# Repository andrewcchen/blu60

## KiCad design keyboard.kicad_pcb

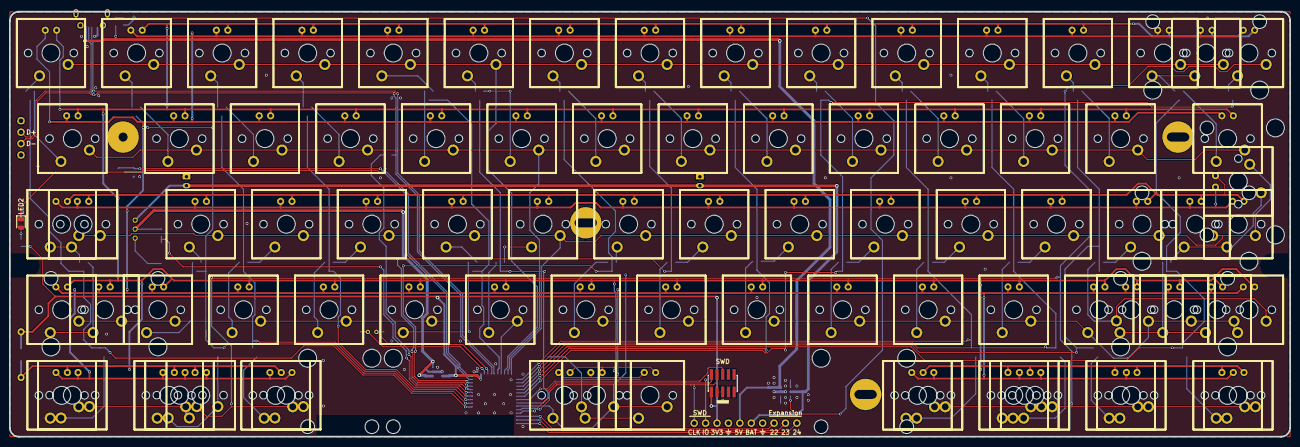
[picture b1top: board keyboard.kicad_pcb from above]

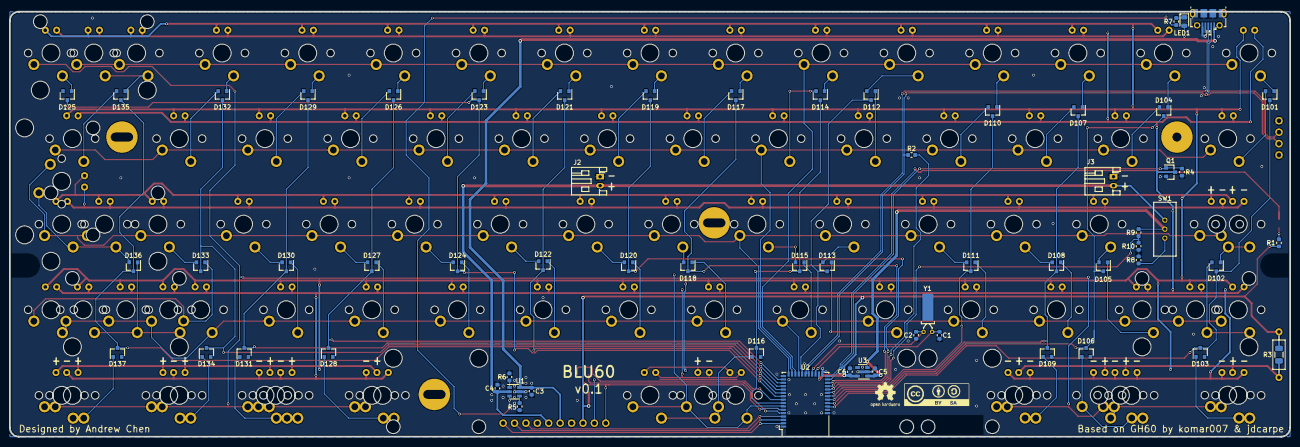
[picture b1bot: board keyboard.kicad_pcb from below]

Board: 2 copper layers, 285.0 x 94.6 mm, 257 parts (64 on the bottom side), 111 nets.

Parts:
C1, C2: C; C_0603_1608Metric
C3, C4, C5, C6: 1uF; C_0603_1608Metric
D101, D102, D104, D105, D107, D108, D110, D111, D112, D113, D114, D115, D117, D118, D119, D120, D121, D122, D123, D124, D126, D127, D129, D130, D132, D133, D135, D136: BAS70-05; SOT-23
D103, D106, D109, D116, D125, D128, D131, D134, D137: BAS70-05; D_SOT-23_ANK
J1: USB_B_Micro; USB_Micro-B_Molex-105017-0001
J2, J3: JST_PH; JST_PH_S2B-PH-K_1x02_P2.00mm_Horizontal
J4: Conn_ARM_JTAG_SWD_10; PinHeader_2x05_P1.27mm_Vertical_SMD
J5: Conn_01x10; PinHeader_1x10_P2.54mm_Vertical
LED1, LED2: Red_LED; LED_0805_2012Metric
LED101, LED102, LED103, LED104, LED105, LED106, LED107, LED108, LED109, LED110, LED111, LED112, LED113, LED114, LED115, LED116, LED117, LED118, LED119, LED120, LED121, LED122, LED123, LED124, LED125, LED126, LED127, LED128, LED129, LED130, LED131, LED132, LED133, LED134, LED135, LED136, LED137, LED138, LED139, LED140, LED141, LED142, LED143, LED144, LED145, LED146, LED147, LED148, LED149, LED150, LED151, LED152, LED153, LED154, LED155, LED156, LED157, LED158, LED159, LED160, LED161, LED162, LED163, LED164, LED165, LED166, LED167, LED168, LED169, LED170, LED171, LED172, LED173, LED174, LED175, LED176, LED177, LED178, LED179, LED180, LED181, LED182, LED183, LED184: LED; MX1A-led_no3d
MK1, MK6: Mounting_Hole; PKRHSL
MK2: Mounting_Hole; PKRHC
MK3, MK4, MK5: Mounting_Hole; PKRH
MXST1, MXST2, MXST3, MXST4, MXST5, MXST6, MXST7, MXST8, MXST9, MXST10, MXST11, MXST12, MXST13, MXST14, MXST15: Cherry_Stabilizer; MXST
Q1: Q_NMOS; SOT-23
R1, R2, R5: 1.5k; R_0603_1608Metric
R3: R; R_Axial_DIN0207_L6.3mm_D2.5mm_P10.16mm_Horizontal
R3#2: R_1206_3216Metric
R4, R9, R10: 100k; R_0603_1608Metric
R6, R7, R8: 10k; R_0603_1608Metric
S101, S102, S103, S105, S107, S109, S110, S111, S113, S116, S117, S118, S119, S120, S122, S123, S124, S125, S126, S127, S128, S129, S130, S131, S132, S133, S134, S137, S138, S139, S140, S141, S142, S143, S144, S145, S146, S147, S148, S149, S150, S151, S152, S154, S155, S156, S157, S158, S160, S161, S162, S163, S164, S167, S168, S173, S174, S176, S177, S180, S184: MX1A
S104, S106, S108, S112, S114, S115, S121, S135, S136, S153, S159, S165, S166, S169, S170, S171, S172, S175, S178, S179, S181, S182, S183: MX1A; MX1A_no3d
SW1: SSSS912000
TP1: TestPoint; PinHeader_1x04_P2.54mm_Vertical
U1: BQ21040; SOT-23-6
U2: BL652; Laird_BL652
U3: TLV70033; SOT-23-5
Y1: 32.768kHz; Crystal_DS26_D2.0mm_L6.0mm_Horizontal_1EP_style1

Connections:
+3V3: C6.1, J4.1, J5.3, R1.1, R3.1, R3#2.1, U2.26, U3.5
/BKLT_LED: Q1.1, R4.1, U2.29
/CAPS_LED: LED2.1, U2.28
/Leds/CAPS_LED+: LED2.2, R1.2
/Leds/LED+: LED101.1, LED102.1, LED103.1, LED104.1, LED105.1, LED106.1, LED107.1, LED108.2, LED109.1, LED110.1, LED111.1, LED112.1, LED113.1, LED114.2, LED115.2, LED116.1, LED117.1, LED118.1, LED119.1, LED120.1, LED121.2, LED122.1, LED123.1, LED124.1, LED125.1, LED126.1, LED127.1, LED128.1, LED129.1, LED130.1, LED131.1, LED132.1, LED133.1, LED134.1, LED135.1, LED136.1, LED137.1, LED138.1, LED139.1, LED140.1, LED141.1, LED142.1, LED143.1, LED144.1, LED145.1, LED146.1, LED147.1, LED148.1, LED149.1, LED150.1, LED151.1, LED152.1, LED153.1, LED154.1, LED155.1, LED156.1, LED157.1, LED158.2, LED159.1, LED160.1, LED161.1, LED162.1, LED163.2, LED164.2, LED165.1, LED166.1, LED167.1, LED168.1, LED169.1, LED170.1, LED171.1, LED172.2, LED173.1, LED174.1, LED175.1, LED176.1, LED177.1, LED178.1, LED179.1, LED180.1, LED181.1, LED182.1, LED183.2, LED184.1, R3.2, R3#2.2
/Leds/LED-: LED101.2, LED102.2, LED103.2, LED104.2, LED105.2, LED106.2, LED107.2, LED108.1, LED109.2, LED110.2, LED111.2, LED112.2, LED113.2, LED114.1, LED115.1, LED116.2, LED117.2, LED118.2, LED119.2, LED120.2, LED121.1, LED122.2, LED123.2, LED124.2, LED125.2, LED126.2, LED127.2, LED128.2, LED129.2, LED130.2, LED131.2, LED132.2, LED133.2, LED134.2, LED135.2, LED136.2, LED137.2, LED138.2, LED139.2, LED140.2, LED141.2, LED142.2, LED143.2, LED144.2, LED145.2, LED146.2, LED147.2, LED148.2, LED149.2, LED150.2, LED151.2, LED152.2, LED153.2, LED154.2, LED155.2, LED156.2, LED157.2, LED158.1, LED159.2, LED160.2, LED161.2, LED162.2, LED163.1, LED164.1, LED165.2, LED166.2, LED167.2, LED168.2, LED169.2, LED170.2, LED171.2, LED172.1, LED173.2, LED174.2, LED175.2, LED176.2, LED177.2, LED178.2, LED179.2, LED180.2, LED181.2, LED182.2, LED183.1, LED184.2, Q1.3
/NCHG: R7.2, U1.3
/SWDCLK: J4.4, J5.1, U2.6
/SWDIO: J4.2, J5.2, U2.5
/SWO: J4.6, U2.9
/USB_D+: J1.3, TP1.2, U2.22
/USB_D-: J1.2, R2.1, TP1.3, U2.23
/USB_PU: R2.2, U2.32
/VBAT: C4.1, J2.2, J3.2, J5.6, SW1.1, U1.2
/VBAT_SENSE: R9.2, R10.1, U2.33
/VBAT_SW: C5.1, R9.1, SW1.2, U3.1, U3.3
/VBUS: C3.1, J1.1, J5.5, LED1.2, U1.6
/col1: D101.3, D102.3, D103.1, U2.37
/col2: D104.3, D105.3, D106.1, U2.36
/col3: D107.3, D108.3, D109.1, U2.35
/col4: D110.3, D111.3, U2.34
/col5: D112.3, D113.3, U2.21
/col6: D114.3, D115.3, D116.1, U2.8
/col7: D117.3, D118.3, U2.30
/col8: D119.3, D120.3, U2.31
/col9: D121.3, D122.3, U2.11
/col10: D123.3, D124.3, D125.1, U2.10
/col11: D126.3, D127.3, D128.1, U2.15
/col12: D129.3, D130.3, D131.1, U2.14
/col13: D132.3, D133.3, D134.1, U2.13
/col14: D135.3, D136.3, D137.1, U2.12
/row1: S101.1, S109.1, S116.1, S122.1, S126.1, S130.1, S137.1, S141.1, S145.1, S149.1, S154.1, S160.1, S167.1, S174.1, S175.1, U2.19
/row2: S102.1, S110.1, S117.1, S123.1, S127.1, S131.1, S138.1, S142.1, S146.1, S150.1, S155.1, S161.1, S168.1, S176.1, U2.18
/row3: S103.1, S104.1, S111.1, S118.1, S124.1, S128.1, S132.1, S139.1, S143.1, S147.1, S151.1, S156.1, S162.1, S169.1, S177.1, S178.1, S179.1, U2.17
/row4: S105.1, S106.1, S112.1, S119.1, S125.1, S129.1, S133.1, S140.1, S144.1, S148.1, S152.1, S157.1, S163.1, S170.2, S171.2, S180.1, S181.1, S182.1, U2.20
/row5: S107.1, S108.1, S113.1, S114.2, S115.1, S120.1, S121.1, S134.1, S135.2, S136.1, S153.1, S158.1, S159.1, S164.1, S165.1, S166.1, S172.1, S173.1, S183.1, S184.1, U2.7
/usr22: J5.8, U2.4
/usr23: J5.9, U2.3
/usr24: J5.10, U2.2
GND: C1.2, C2.2, C3.2, C4.2, C5.2, C6.2, J1.5, J1.6, J2.1, J3.1, J4.3, J4.5, J4.9, J5.4, J5.7, Q1.2, R4.2, R5.2, R6.1, R8.2, R10.2, TP1.1, TP1.4, U1.5, U2.1, U2.16, U2.27, U2.39, U3.2
unnamed: C1.1, U2.25, Y1.1
unnamed: C2.1, U2.24, Y1.2
unnamed: D101.1, S101.2
unnamed: D101.2, S102.2
unnamed: D102.1, S103.2, S104.2
unnamed: D102.2, S105.2, S106.2
unnamed: D103.2, S107.2, S108.2
unnamed: D104.1, S109.2
unnamed: D104.2, S110.2
unnamed: D105.1, S112.2
unnamed: D105.2, S111.2
unnamed: D106.2, S113.2, S114.1, S115.2
unnamed: D107.1, S116.2
unnamed: D107.2, S117.2
unnamed: D108.1, S119.2
unnamed: D108.2, S118.2
unnamed: D109.2, S120.2, S121.2
unnamed: D110.1, S122.2
unnamed: D110.2, S123.2
unnamed: D111.1, S125.2
unnamed: D111.2, S124.2
unnamed: D112.1, S127.2
unnamed: D112.2, S126.2
unnamed: D113.1, S129.2
unnamed: D113.2, S128.2
unnamed: D114.1, S130.2
unnamed: D114.2, S131.2
unnamed: D115.1, S133.2
unnamed: D115.2, S132.2
unnamed: D116.2, S134.2, S135.1, S136.2
unnamed: D117.1, S137.2
unnamed: D117.2, S138.2
unnamed: D118.1, S140.2
unnamed: D118.2, S139.2
unnamed: D119.1, S141.2
unnamed: D119.2, S142.2
unnamed: D120.1, S144.2
unnamed: D120.2, S143.2
unnamed: D121.1, S145.2
unnamed: D121.2, S146.2
unnamed: D122.1, S148.2
unnamed: D122.2, S147.2
unnamed: D123.1, S149.2
unnamed: D123.2, S150.2
unnamed: D124.1, S152.2
unnamed: D124.2, S151.2
unnamed: D125.2, S153.2
unnamed: D126.1, S154.2
unnamed: D126.2, S155.2
unnamed: D127.1, S157.2
unnamed: D127.2, S156.2
unnamed: D128.2, S158.2, S159.2
unnamed: D129.1, S160.2
unnamed: D129.2, S161.2
unnamed: D130.1, S163.2
unnamed: D130.2, S162.2
unnamed: D131.2, S164.2, S165.2, S166.2
unnamed: D132.1, S167.2
unnamed: D132.2, S168.2
unnamed: D133.1, S170.1, S171.1
unnamed: D133.2, S169.2
unnamed: D134.2, S172.2, S173.2
unnamed: D135.1, S174.2, S175.2
unnamed: D135.2, S176.2
unnamed: D136.1, S180.2, S181.2, S182.2
unnamed: D136.2, S177.2, S178.2, S179.2
unnamed: D137.2, S183.2, S184.2
unnamed: LED1.1, R7.1
unnamed: R5.1, U1.4
unnamed: R6.2, U1.1
unnamed: R8.1, SW1.3

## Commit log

2018-07-08 import
2018-07-08 stupid paths
2018-08-10 finally completed?
2018-08-10 cleanup
2018-08-12 almost ready
2018-08-12 I think we are ready
2018-08-12 Final touchups
2018-08-12 Really final touchups
2018-08-13 Fixing up my stupid mistake
2018-08-13 Silkscreen changes
2018-08-15 v0.1 release
2018-09-04 mechanical changes
    - moved micro usb connector up 1.1mm
    - made micro usb pads 1mm longer
    - changed mounting hole drill from 2.5mm to 2mm
2018-09-05 tweaked thermal reliefs
